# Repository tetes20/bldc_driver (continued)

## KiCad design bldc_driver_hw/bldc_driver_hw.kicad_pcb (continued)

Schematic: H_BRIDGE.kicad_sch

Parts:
C51: C_Small; C_1206_3216Metric; not fitted
C52: C_Snub; C_1206_3216Metric; not fitted
C90: 1uF; C_0603_1608Metric; LCSC C15849
C93: 100nF; C_0603_1608Metric; LCSC C14663
C94: 10uF; C_0603_1608Metric; LCSC C96446
D7, D8, D20: SS54; D_SMA; LCSC C22452
D9, D10: D_Schottky; D_SMB; not fitted
Q1, Q2: IPB026N06NATMA1; TO-263-2
R33, R34: 33R; R_0805_2012Metric; LCSC C17634
R35, R36: 0R; R_0805_2012Metric; LCSC C17477
R37, R38: 100k; R_0805_2012Metric; LCSC C149504
R39, R40, R41: 30m; R_2512_6332Metric
R42, R43: R_SNUB; R_1206_3216Metric; not fitted
R105, R108: 10k; R_0603_1608Metric; LCSC C25804
TP30, TP31: TestPoint; TestPoint_Pad_D2.0mm
U15: UCC27288; SOIC-8_3.9x4.9mm_P1.27mm

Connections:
+12V: C93.1, C94.1, D20.2 (A), U15.1 (VDD); also elsewhere on the board
+48V: D9.1 (K), Q1.2 (D), R42.2; also elsewhere on the board
/BEMF_SENS/PHASE_U: C51.1, C52.1, R39.2, R40.2, R41.2; also elsewhere on the board
/MCU/IN_H_U: R105.1, U15.5 (HI); also elsewhere on the board
/MCU/IN_L_U: R108.1, U15.6 (LI); also elsewhere on the board
/MOTOR_CTRL/CSA2/CSA_P: C90.2, D9.2 (A), D10.1 (K), Q1.3 (S), Q2.2 (D), R38.1, R39.1, R40.1, R41.1, U15.4 (HS); also elsewhere on the board
GND: C93.2, C94.2, D10.2 (A), Q2.3 (S), R37.1, R43.2, R105.2, R108.2, U15.7 (VSS); also elsewhere on the board
unnamed: C51.2, R42.1
unnamed: C52.2, R43.1
unnamed: D7.2 (A), R35.2
unnamed: D7.1 (K), R33.1, U15.3 (HO)
unnamed: D8.2 (A), R36.1
unnamed: D8.1 (K), R34.1, U15.8 (LO)
unnamed: C90.1, D20.1 (K), U15.2 (HB)
unnamed: Q1.1 (G), R33.2, R35.1, R38.2, TP30.1
unnamed: Q2.1 (G), R34.2, R36.2, R37.2, TP31.1

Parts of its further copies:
C53, C55: C_Small; C_1206_3216Metric; not fitted
C54, C56: C_Snub; C_1206_3216Metric; not fitted
C91, C92: 1uF; C_0603_1608Metric; LCSC C15849
C95, C97: 100nF; C_0603_1608Metric; LCSC C14663
C96, C98: 10uF; C_0603_1608Metric; LCSC C96446
D11, D12, D15, D16, D21, D22: SS54; D_SMA; LCSC C22452
D13, D14, D17, D18: D_Schottky; D_SMB; not fitted
Q3, Q4, Q5, Q6: IPB026N06NATMA1; TO-263-2
R44, R45, R55, R56: 33R; R_0805_2012Metric; LCSC C17634
R46, R47, R57, R58: 0R; R_0805_2012Metric; LCSC C17477
R48, R49, R59, R60: 100k; R_0805_2012Metric; LCSC C149504
R50, R51, R52, R61, R62, R63: 30m; R_2512_6332Metric
R53, R54, R64, R65: R_SNUB; R_1206_3216Metric; not fitted
R106, R107, R109, R110: 10k; R_0603_1608Metric; LCSC C25804
TP32, TP33, TP34, TP35: TestPoint; TestPoint_Pad_D2.0mm
U16, U17: UCC27288; SOIC-8_3.9x4.9mm_P1.27mm

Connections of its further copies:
+12V: C95.1, C96.1, C97.1, C98.1, D21.2 (A), D22.2 (A), U16.1 (VDD), U17.1 (VDD); also elsewhere on the board
+48V: D13.1 (K), D17.1 (K), Q3.2 (D), Q5.2 (D), R53.2, R64.2; also elsewhere on the board
/BEMF_SENS/PHASE_V: C55.1, C56.1, R61.2, R62.2, R63.2; also elsewhere on the board
/BEMF_SENS/PHASE_W: C53.1, C54.1, R50.2, R51.2, R52.2; also elsewhere on the board
/MCU/IN_H_V: R107.1, U17.5 (HI); also elsewhere on the board
/MCU/IN_H_W: R106.1, U16.5 (HI); also elsewhere on the board
/MCU/IN_L_V: R110.1, U17.6 (LI); also elsewhere on the board
/MCU/IN_L_W: R109.1, U16.6 (LI); also elsewhere on the board
/MOTOR_CTRL/CSA1/CSA_P: C91.2, D13.2 (A), D14.1 (K), Q3.3 (S), Q4.2 (D), R49.1, R50.1, R51.1, R52.1, U16.4 (HS); also elsewhere on the board
/MOTOR_CTRL/CSA/CSA_P: C92.2, D17.2 (A), D18.1 (K), Q5.3 (S), Q6.2 (D), R60.1, R61.1, R62.1, R63.1, U17.4 (HS); also elsewhere on the board
GND: C95.2, C96.2, C97.2, C98.2, D14.2 (A), D18.2 (A), Q4.3 (S), Q6.3 (S), R48.1, R54.2, R59.1, R65.2, R106.2, R107.2, R109.2, R110.2, U16.7 (VSS), U17.7 (VSS); also elsewhere on the board
unnamed: C53.2, R53.1
unnamed: C54.2, R54.1
unnamed: C55.2, R64.1
unnamed: C56.2, R65.1
unnamed: D11.2 (A), R46.2
unnamed: D11.1 (K), R44.1, U16.3 (HO)
unnamed: D12.2 (A), R47.1
unnamed: D12.1 (K), R45.1, U16.8 (LO)
unnamed: D15.2 (A), R57.2
unnamed: D15.1 (K), R55.1, U17.3 (HO)
unnamed: D16.2 (A), R58.1
unnamed: D16.1 (K), R56.1, U17.8 (LO)
unnamed: C91.1, D21.1 (K), U16.2 (HB)
unnamed: C92.1, D22.1 (K), U17.2 (HB)
unnamed: Q3.1 (G), R44.2, R46.1, R49.2, TP32.1
unnamed: Q4.1 (G), R45.2, R47.2, R48.2, TP33.1
unnamed: Q5.1 (G), R55.2, R57.1, R60.2, TP34.1
unnamed: Q6.1 (G), R56.2, R58.2, R59.2, TP35.1

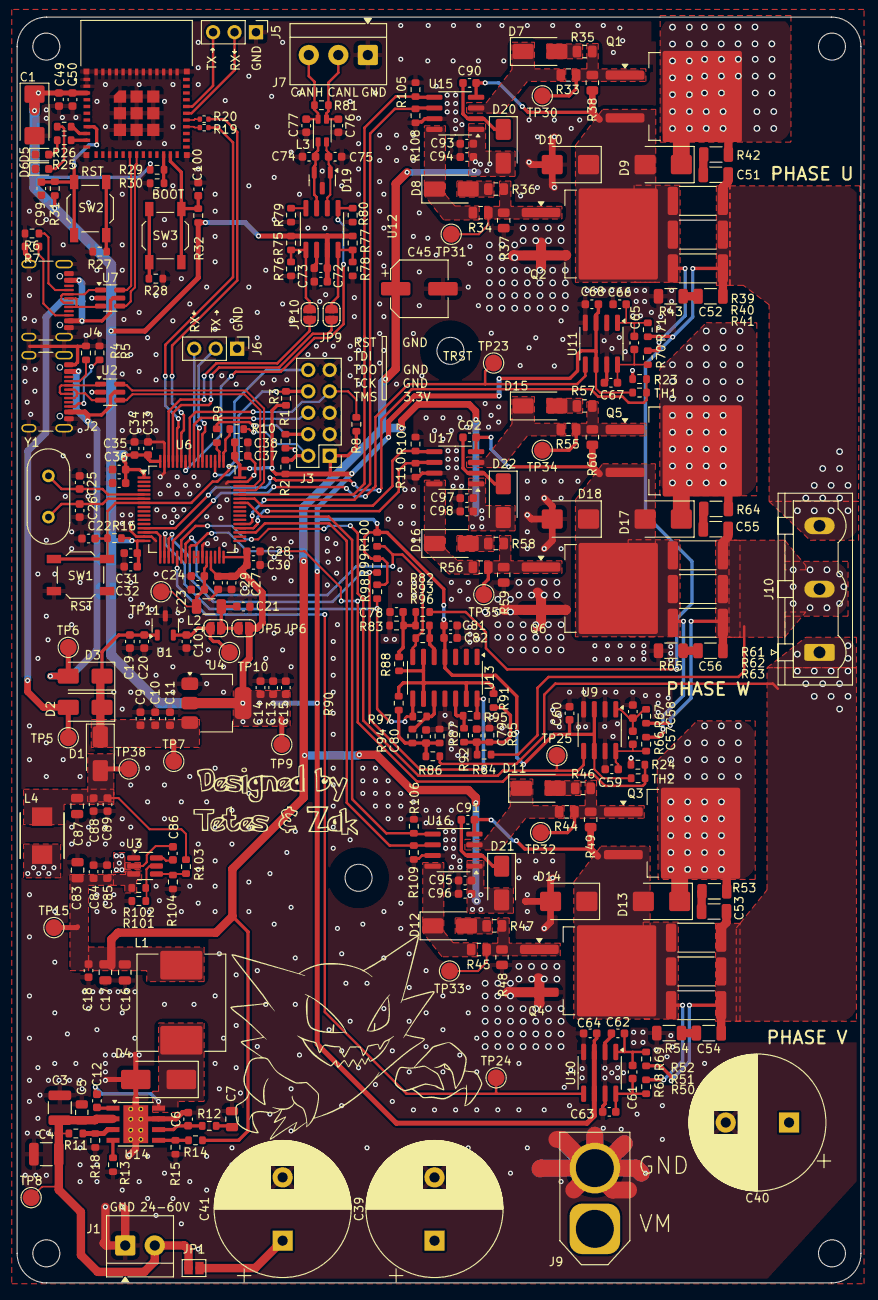
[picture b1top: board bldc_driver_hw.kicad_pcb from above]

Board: 2 copper layers, 100.0 x 150.0 mm, 285 parts (0 on the bottom side), 133 nets.

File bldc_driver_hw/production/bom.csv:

Designator,Footprint,Quantity,Value,LCSC Part #
"C10, C13, C14, C19, C27, C28, C31, C34, C36, C38, C49, C73, C81, C84, C88, C9, C94, C96, C98",0603,19,10uF,C96446
"C100, C11, C12, C15, C18, C20, C21, C22, C24, C29, C30, C32, C33, C35, C37, C50, C60, C64, C68, C72, C82, C85, C86, C89, C93, C95, C97, C99",0603,28,100nF,C14663
"C101, C23, C90, C91, C92",0603,5,1uF,C15849
"C16, C17, C83, C87",0805,4,22uF,C45783
"C25, C26",0603,2,18pF,C1647
C5,0805,1,100nF 75V,C28233
C6,0603,1,10pF,C1634
C7,0805,1,2.2nF,C28260
"C74, C75, C76, C77",0603,4,33pF,C1663
"D1, D11, D12, D15, D16, D2, D20, D21, D22, D3, D7, D8",D_SMA,12,SS54,C22452
"D5, D6",0603,2,LED,C2286
"R1, R100, R101, R102, R104, R105, R106, R107, R108, R109, R110, R2, R23, R24, R25, R26, R27, R28, R29, R3, R30, R31, R32, R8, R98, R99",0603,26,10k,C25804
"R10, R9",0603,2,47R,C23182
R103,0603,1,56k,C23206
"R12, R82, R84, R86",0603,4,47k,C25819
"R16, R18, R80, R88, R90, R91",0603,6,100k,C25803
"R19, R20",0402,2,0R,C17168
"R33, R34, R44, R45, R55, R56",0805,6,33R,C17634
"R35, R36, R46, R47, R57, R58",0805,6,0R,C17477
"R37, R38, R48, R49, R59, R60",0805,6,100k,C149504
"R4, R5, R6, R7",0603,4,5.1k,C23186
"R66, R67, R68, R69, R70, R71, R79, R92, R93, R94",0603,10,0R,C21189
"R83, R85, R87",0603,3,3k,C4211
"R95, R96, R97",0603,3,510k,C23192
"SW1, SW2, SW3",SW_SPST_TL3342,3,SW_Push,C318884
U4,SOT-223-3_TabPin2,1,AMS1117-3.3,C6186

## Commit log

2025-04-03 hw init
2025-04-08 schematic finished pcb in progress
2025-04-08 Changed one 3 phase driver to three h-bridges and changed buck converter which sink more current
2025-04-09 Board finished to review
2025-04-10 board finished
2025-04-15 added lcsc codes
2025-04-15 finished_board
2025-04-15 finished
2025-04-16 Changed size of capacitors at input 48V dc converter
2025-04-16 changed vref
2025-04-18 changed hrtim to tim1
